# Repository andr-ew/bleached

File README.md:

## bleached
small/inexpensive 7-knob teensy midi controller. 

many thanks to [brian crabtree](https://vimeo.com/134631071) for sending me the original design & helping me add the teensy !!

## BOM

- [full BOM other than knobs](https://octopart.com/bom-tool/u6LfSTSI)
- [knobs from thonk (uk)](https://www.thonk.co.uk/shop/intellijel-black-knobs/) - [caps](https://www.thonk.co.uk/shop/sifam-caps/)

## Build

start with soldering all header pins to the underside of the teensy 3.2, reference the pic below for placement. the goal is to hit all of the power/ground pinouts along with the analog ins. solder short sides the two through-hole pins to the teensy. 

getting the surface mount pins in the right place is the trickiest part of this project. start with those (one leg at a time), use tweezers, and test placement on the board with the through-hole headers.

the rest should be pretty easy, solder all the other headers to the teensy, solder the teensy to the board (on the top / stencil side of the board), and solder every leg of each of the pots. load firmware & test once everything is soldered (although, at this point there's kinda no going back) - you can test your pots by loading the [test_inputs](./firmware/test_inputs/test_inputs.ino) sketch onto the board, and looking at the serial monitor window (Tools -> Serial Monitor) while twiddling the knobs. the firmware is an arduino project for use with [teensyduino](https://www.pjrc.com/teensy/teensyduino.html). 

next, add the metal standoffs, shorter ones on the bottom, taller ones on top. then screw in the panels. if you want the pots extra stable you can add the nuts and washers that come with the potentiometers. then plop on yr favorite knobs & yr golden !

## FAQ

q1) i don't have a 5-pin header for the top end of the teensy.
a2) you should have a 3-pin header, which should be used with the 3 middle pins.

q2) i get an error compiling the firmware, `'usbMIDI' was not declared in this scope`.
a2) set the USB type to 'Serial + MIDI' on the Tools -> USB Type menu.

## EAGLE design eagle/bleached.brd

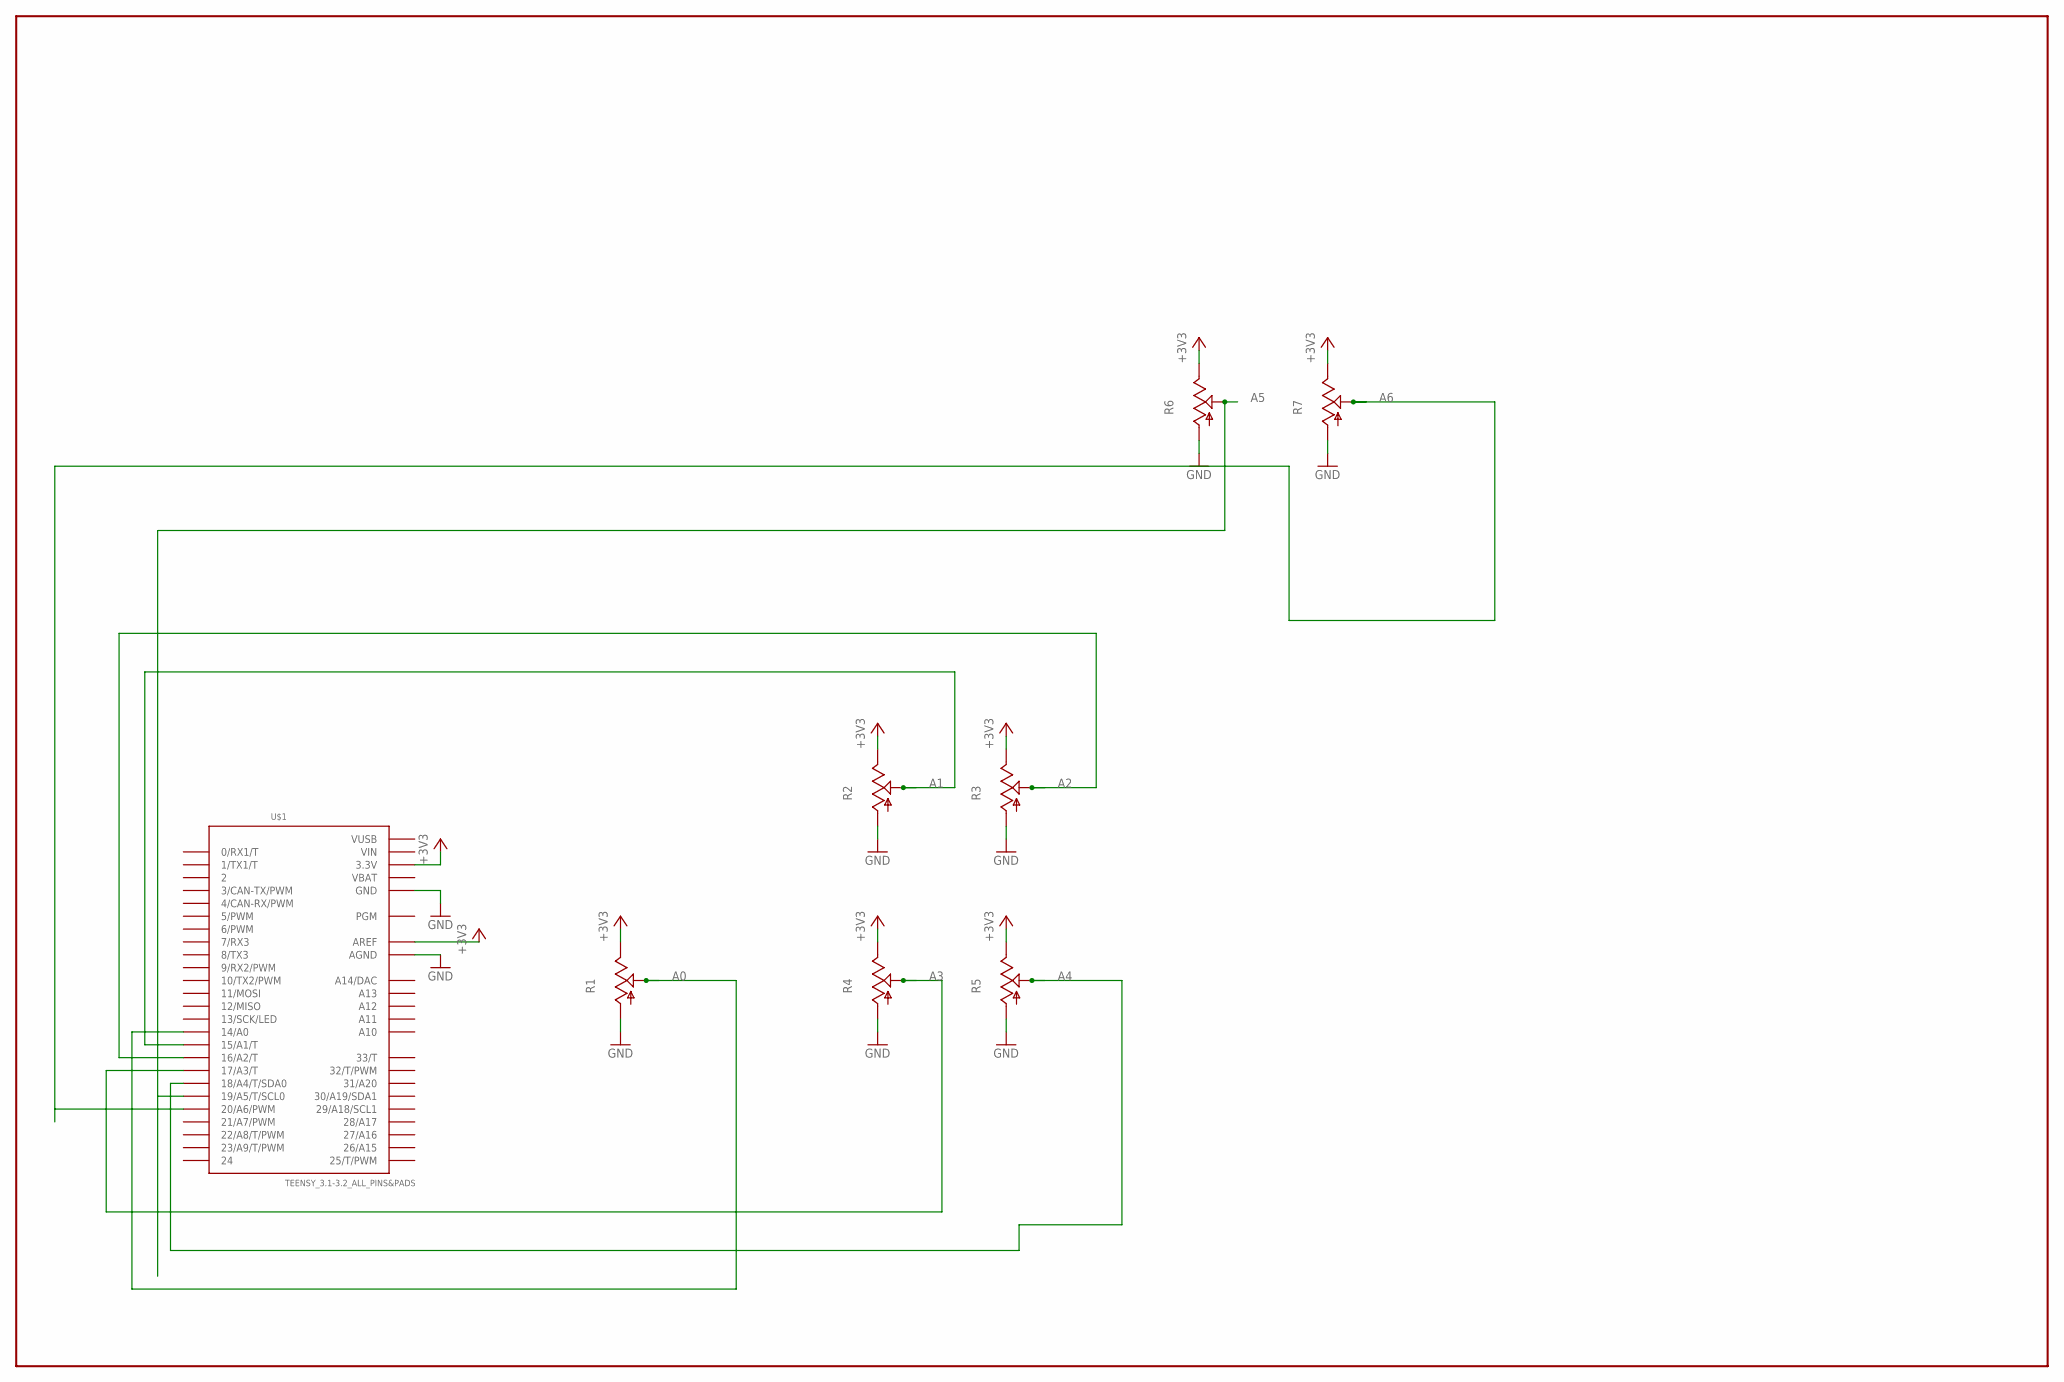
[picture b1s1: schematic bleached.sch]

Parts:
R1, R2, R3, R4, R5, R6, R7: SHAPES_POT-ALPS_POT_USVERTICAL_PS; SHAPES_POT-ALPS_ALPS_POT_VERTICAL_PS
U$1: TEENSY_3.1-3.2_ALL_PINS&PADS; TEENSY_3.0-3.2_ALL_PINS_&_PADS

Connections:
+3V3: R1.P$1 (E), R2.P$1 (E), R3.P$1 (E), R4.P$1 (E), R5.P$1 (E), R6.P$1 (E), R7.P$1 (E), U$1.3.3V, U$1.3.3V1 (3.3V), U$1.3.3V2 (3.3V), U$1.AREF
A0: R1.P$2 (S), U$1.14/A0
A1: R2.P$2 (S), U$1.15/A1 (15/A1/T)
A2: R3.P$2 (S), U$1.16/A2 (16/A2/T)
A3: R4.P$2 (S), U$1.17/A3 (17/A3/T)
A4: R5.P$2 (S), U$1.18/A4 (18/A4/T/SDA0)
A5: R6.P$2 (S), U$1.19/A5 (19/A5/T/SCL0)
A6: R7.P$2 (S), U$1.20/A6 (20/A6/PWM)
GND: R1.P$3 (A), R2.P$3 (A), R3.P$3 (A), R4.P$3 (A), R5.P$3 (A), R6.P$3 (A), R7.P$3 (A), U$1.AGND, U$1.GND, U$1.GND1 (GND), U$1.GND2 (GND)
VBAT: U$1.VBAT
VIN: U$1.VIN
VUSB: U$1.VUSB

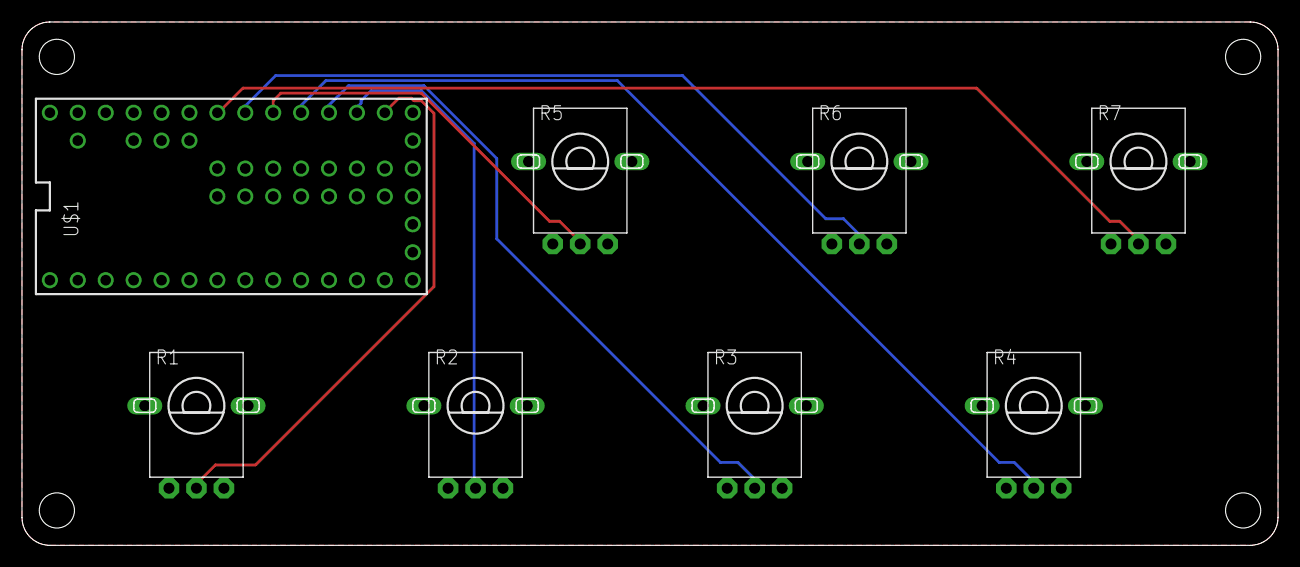
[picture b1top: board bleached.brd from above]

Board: 2 copper layers, 114.3 x 47.6 mm, 8 parts (0 on the bottom side), 9 nets.

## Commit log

2020-02-12 eagles
2020-02-12 panels
2020-02-22 firmware !
2020-06-22 fixed pot holes, added images
2020-06-22 crop
2020-06-22 crop2
2020-07-18 Added missing pot and removed non-existing ones
2020-07-18 Added note about testing and faqs
2021-10-07 read midi input, avoiding issues from always-full buffer
